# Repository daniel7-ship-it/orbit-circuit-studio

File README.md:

# ORBIT — Circuit Studio

A browser-based circuit and PCB editor focused on simple interactions: place parts, pull wires, simulate, and lay out a board. 

**Status:** working prototype under active development.

## Try it locally

This repository contains the source code; it does not currently provide a public live demo. To run the app on your computer, download or clone this repository and open a terminal in its folder.

No dependency installation or build step is needed. With Python 3 installed:

```sh
python3 -m http.server 5173 --bind 127.0.0.1 --directory dist
```

Keep that terminal running, then enter `http://127.0.0.1:5173` in your browser on the same computer. This is a local address, not a hosted website; it will only work while the server is running. The app starts with an RC circuit.

1. **Design:** add resistors, capacitors, a voltage source, and ground. Drag parts to move them; pull between pins to connect. Each schematic part has a rotate indicator.
2. **Simulate:** run the circuit to view DC results and its step response.
3. **Board:** arrange physical parts and pull between matching pads to route copper. Dashed guides show connections that still need routing. Use **Check connections** to find routing and spacing issues.
4. **More:** change copper layer, trace width, and board dimensions, or export a native KiCad PCB file.

Edits autosave in your browser. Save/import JSON projects to move them between browsers. Command/Ctrl-Z undoes changes; Escape cancels wiring. On the schematic, scroll to zoom and hold Space while dragging to pan.

## Implemented features

- Schematic editing with explicit pin connectivity, editable values, rotation, undo, and JSON import/export.
- DC operating-point simulation using modified nodal analysis.
- Linear RC transient simulation using backward Euler integration.
- PCB placement stored separately from the schematic, in millimeters.
- Top and bottom copper routing with through-hole pads and drills.
- Same-net routing checks, disconnected-net checks, basic copper clearance and board-edge checks.
- Native `.kicad_pcb` export with embedded custom footprints.

The voltage source becomes a two-pin power connector on the PCB. Ground is a reference connection and has no physical footprint. Moving or rotating a board part clears its attached traces so they can be redrawn.

## Example project

Import [the schematic example](evidence/rc-project.json) or [the routed board project](evidence/rc-routed.json).

The example has a **5 V source, 1 kΩ resistor, and 1 µF capacitor**, giving a time constant of **1 ms**. Its capacitor voltage approaches 5 V and reaches about 3.16 V after one time constant; the numerical integration approximates that response.

An [exported board](evidence/rc-board.kicad_pcb) and a [rotated export](evidence/rc-rotated.kicad_pcb) are included. Both sample boards were checked with KiCad 9.0.7 and reported zero violations and zero unconnected items. The corresponding reports are in `evidence/`. Those results apply to these fixtures, not every board created with the editor.

## Validation

With Node.js installed:

```sh
node solver.test.mjs
node pcb.test.mjs
```

Simulation tests compare an equal-resistor divider and RC circuit against analytical values, and check missing ground, unconnected pins, and floating-node errors. PCB tests cover physical pads, refusal to connect different nets, routed connectivity, independent placement, schematic synchronization, edge violations, and crossing traces. PCB tests regenerate the sample board files.

To independently check the exported sample with KiCad's CLI:

```sh
kicad-cli pcb drc --exit-code-violations evidence/rc-board.kicad_pcb
```

## Current limitations

- Simulation supports resistors, capacitors, and ideal voltage sources; semiconductor models, AC sweeps, and a general SPICE engine are not implemented.
- Transient analysis uses a fixed 20 ms window with 50 µs steps, zero initial capacitor voltage, and voltage sources stepping on at time zero.
- The output probe is fixed to the first capacitor's first pin relative to ground, falling back to a resistor or source.
- PCB footprints are fixed: a 7.62 mm resistor, 2.5 mm capacitor, and 2.54 mm power connector. Match actual component dimensions before fabrication.
- There are no vias, copper pours, arbitrary footprint libraries, or direct Gerber export. Continue in KiCad for final checking and manufacturing output.
- Board checks cover a limited set of constraints. Verify footprints against datasheets and run KiCad DRC before ordering hardware.
- Projects are browser-local, with up to 60 components and 200 schematic wires. There is no collaboration backend.

## Code map

| File | Purpose |
| --- | --- |
| `dist/app.js` | Editor state, schematic interactions, and UI |
| `dist/solver.mjs` | DC and transient circuit solver |
| `dist/pcb.mjs` | Physical board model, routing, checks, and KiCad export |
| `dist/index.html`, `dist/styles.css` | Accessible controls and monochrome interface |
| `solver.test.mjs`, `pcb.test.mjs` | Numerical and PCB regression checks |

The app uses plain HTML, CSS, JavaScript modules, and SVG. Google Fonts supplies the interface fonts.

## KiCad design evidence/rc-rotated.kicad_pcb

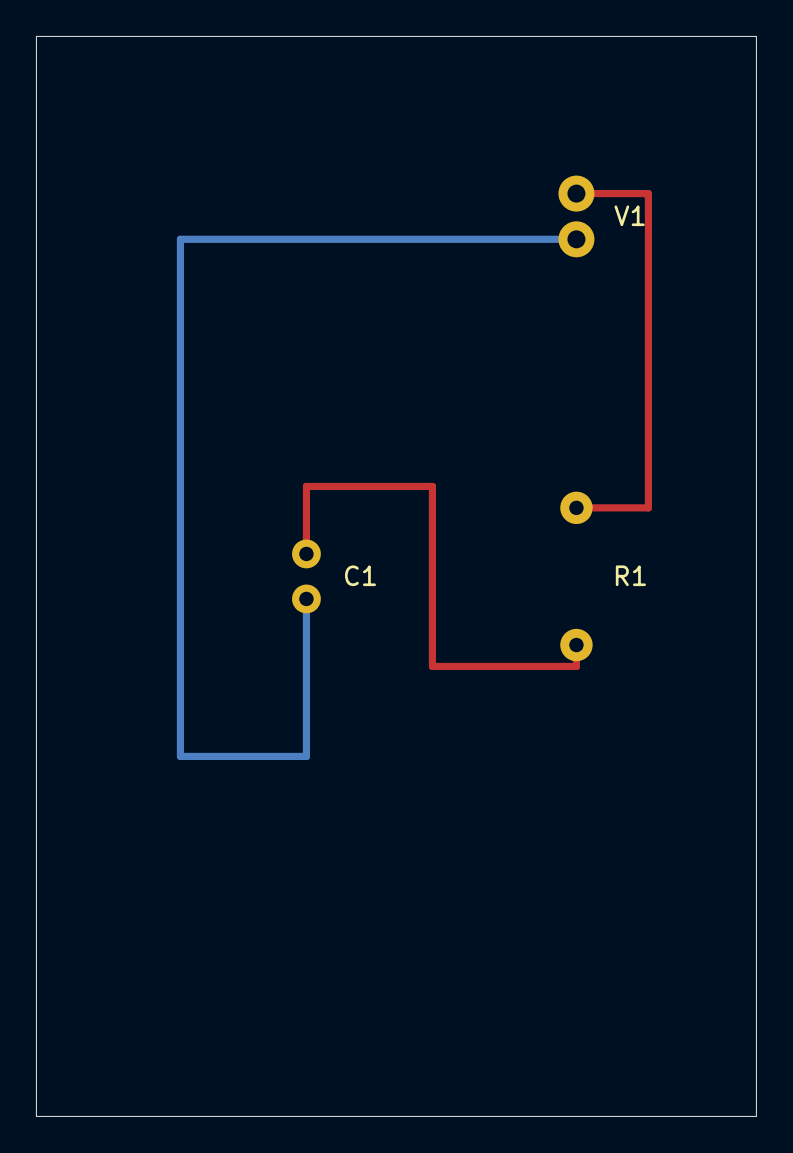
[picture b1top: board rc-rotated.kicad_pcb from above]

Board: 2 copper layers, 40.0 x 60.0 mm, 3 parts (0 on the bottom side), 3 nets.

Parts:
C1: 0.000001; ORBIT_Capacitor_2.50mm
R1: 1000; ORBIT_Resistor_7.62mm
V1: 5; ORBIT_Source_2.54mm

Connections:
GND: C1.2, V1.2
unnamed: C1.1, R1.2
unnamed: R1.1, V1.1
